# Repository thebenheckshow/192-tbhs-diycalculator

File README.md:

# 192-tbhs-diycalculator
Ben, Felix and Max take us back to 1972 and the invention of the first calculator this week, then decide to hack their own! Watch as they use the Raspberry Pi Compute Module and a Formlabs SLA 3D printer to create their own graphing calculator.

https://www.element14.com/community/docs/DOC-77309/l/episode-192-ben-hecks-diy-calculator-episode

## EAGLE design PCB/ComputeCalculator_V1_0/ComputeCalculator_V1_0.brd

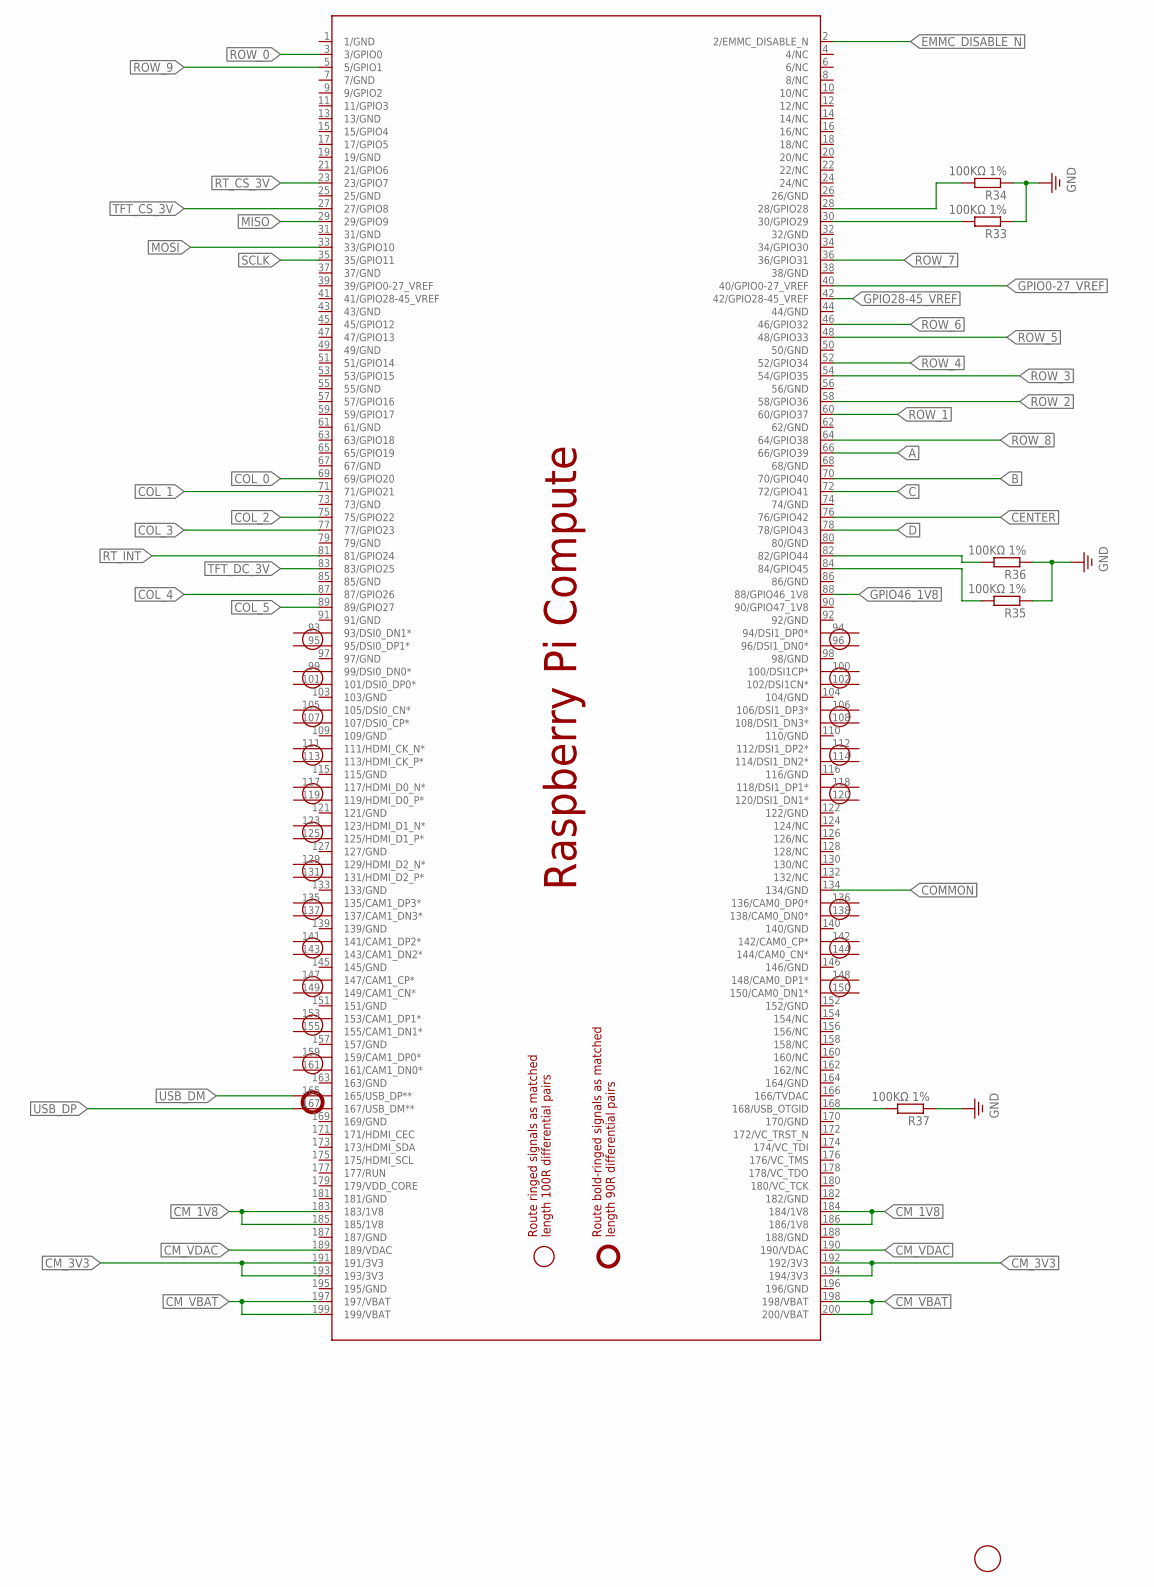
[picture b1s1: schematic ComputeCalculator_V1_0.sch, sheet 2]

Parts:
PCB1: RPI_COMPUTE
R33, R34, R35, R36, R37: 100KΩ 1%; M1206
U$2: FIDUCIAL; FIDUCIAL_1MM

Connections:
A: PCB1.66 (66/GPIO39); also elsewhere on the board
B: PCB1.70 (70/GPIO40); also elsewhere on the board
C: PCB1.72 (72/GPIO41); also elsewhere on the board
CENTER: PCB1.76 (76/GPIO42); also elsewhere on the board
CM_1V8: PCB1.183 (183/1V8), PCB1.184 (184/1V8), PCB1.185 (185/1V8), PCB1.186 (186/1V8); also elsewhere on the board
CM_3V3: PCB1.191 (191/3V3), PCB1.192 (192/3V3), PCB1.193 (193/3V3), PCB1.194 (194/3V3); also elsewhere on the board
CM_VBAT: PCB1.197 (197/VBAT), PCB1.198 (198/VBAT), PCB1.199 (199/VBAT), PCB1.200 (200/VBAT); also elsewhere on the board
CM_VDAC: PCB1.189 (189/VDAC), PCB1.190 (190/VDAC); also elsewhere on the board
COL_0: PCB1.69 (69/GPIO20); also elsewhere on the board
COL_1: PCB1.71 (71/GPIO21); also elsewhere on the board
COL_2: PCB1.75 (75/GPIO22); also elsewhere on the board
COL_3: PCB1.77 (77/GPIO23); also elsewhere on the board
COL_4: PCB1.87 (87/GPIO26); also elsewhere on the board
COL_5: PCB1.89 (89/GPIO27); also elsewhere on the board
COMMON: PCB1.134 (134/GND); also elsewhere on the board
D: PCB1.78 (78/GPIO43); also elsewhere on the board
EMMC_DISABLE_N: PCB1.2 (2/EMMC_DISABLE_N)
GND: R33.1, R34.1, R35.1, R36.1, R37.1; also elsewhere on the board
GPIO0-27_VREF: PCB1.40 (40/GPIO0-27_VREF); also elsewhere on the board
GPIO28-45_VREF: PCB1.42 (42/GPIO28-45_VREF); also elsewhere on the board
GPIO46_1V8: PCB1.88 (88/GPIO46_1V8)
MISO: PCB1.29 (29/GPIO9); also elsewhere on the board
MOSI: PCB1.33 (33/GPIO10); also elsewhere on the board
unnamed: PCB1.28 (28/GPIO28), R34.2
unnamed: PCB1.82 (82/GPIO44), R36.2
unnamed: PCB1.84 (84/GPIO45), R35.2
unnamed: PCB1.168 (168/USB_OTGID), R37.2
unnamed: PCB1.30 (30/GPIO29), R33.2
ROW_0: PCB1.3 (3/GPIO0); also elsewhere on the board
ROW_1: PCB1.60 (60/GPIO37); also elsewhere on the board
ROW_2: PCB1.58 (58/GPIO36); also elsewhere on the board
ROW_3: PCB1.54 (54/GPIO35); also elsewhere on the board
ROW_4: PCB1.52 (52/GPIO34); also elsewhere on the board
ROW_5: PCB1.48 (48/GPIO33); also elsewhere on the board
ROW_6: PCB1.46 (46/GPIO32); also elsewhere on the board
ROW_7: PCB1.36 (36/GPIO31); also elsewhere on the board
ROW_8: PCB1.64 (64/GPIO38); also elsewhere on the board
ROW_9: PCB1.5 (5/GPIO1); also elsewhere on the board
RT_CS_3V: PCB1.23 (23/GPIO7); also elsewhere on the board
RT_INT: PCB1.81 (81/GPIO24); also elsewhere on the board
SCLK: PCB1.35 (35/GPIO11); also elsewhere on the board
TFT_CS_3V: PCB1.27 (27/GPIO8); also elsewhere on the board
TFT_DC_3V: PCB1.83 (83/GPIO25); also elsewhere on the board
USB_DM: PCB1.165 (165/USB_DP**); also elsewhere on the board
USB_DP: PCB1.167 (167/USB_DM**); also elsewhere on the board

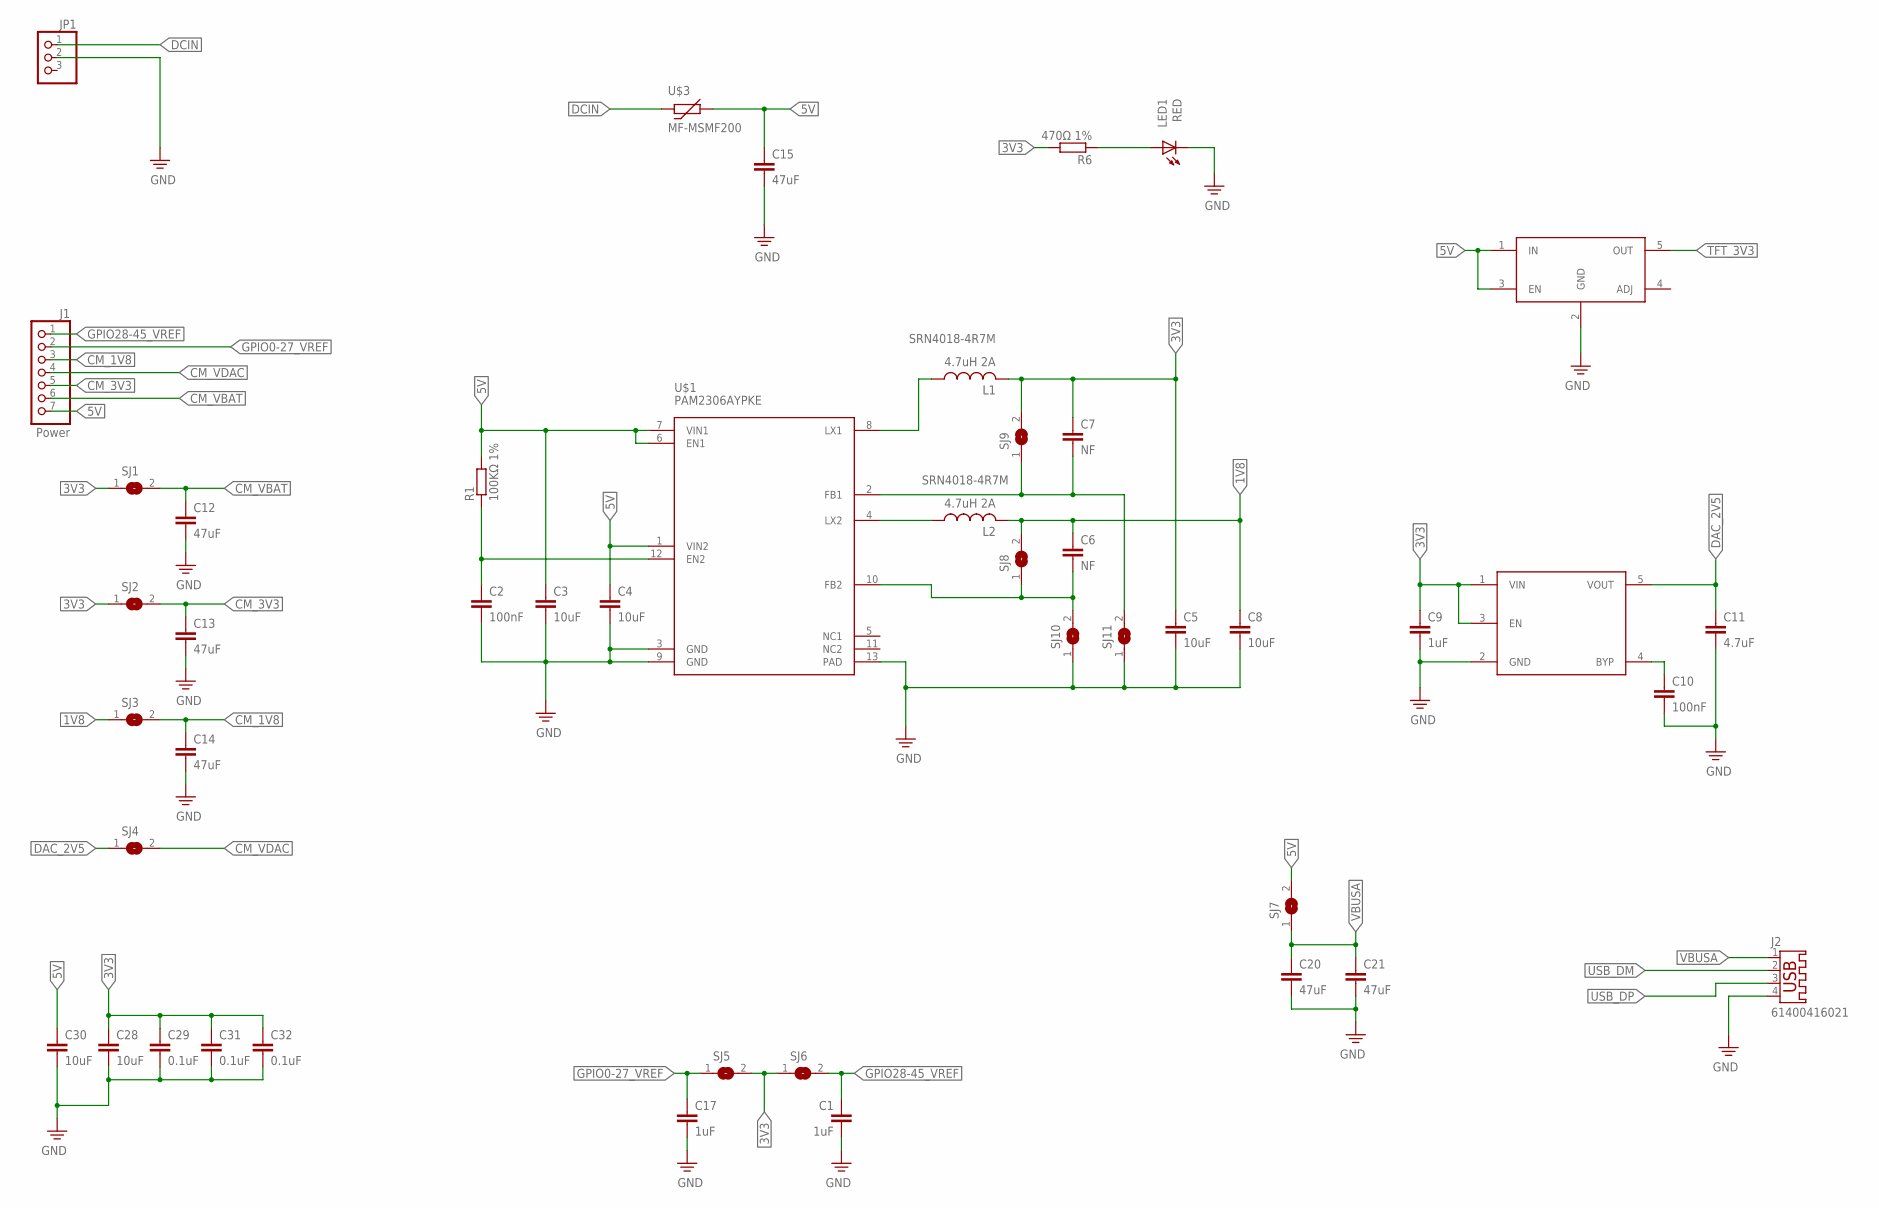
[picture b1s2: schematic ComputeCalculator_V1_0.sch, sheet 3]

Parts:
C1, C9, C17: 1uF; C1206
C2, C10: 100nF; C1206
C3, C4, C5, C8, C28, C30: 10uF; C1206
C6, C7: NF; C1206
C11: 4.7uF; C1206
C12, C13, C14, C20, C21: 47uF; C1206
C15: 47uF; C0603
C29, C31, C32: 0.1uF; C1206
J1: Power; 1X7-BIG
J2: 61400416021; USB-A003
JP1: PINHD-1X3; 1X03
L1, L2: SRN4018-4R7M; POWER-CHOKE_WE-TPC
LED1: RED; CHIP-LED0805
R1: 100KΩ 1%; M1206
R6: 470Ω 1%; M1206
SJ1, SJ2, SJ3, SJ4, SJ5, SJ6, SJ7, SJ8, SJ9, SJ10, SJ11: JUMPER; SJW
U$1: PAM2306AYPKE; WDFN_12L
U$3: MF-MSMF200
U$4: AP7115-25SEG; SOT-25
U$5: MIC5225; SOT-25

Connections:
1V8: C6.1, C8.1, L2.2, SJ3.1, SJ8.2
3V3: C5.1, C7.1, C9.1, C28.1, C29.1, C31.1, C32.1, L1.2, R6.2, SJ1.1, SJ2.1, SJ5.2, SJ6.1, SJ9.2, U$4.1 (VIN), U$4.3 (EN)
5V: C3.1, C4.1, C15.1, C30.1, J1.7, R1.2, SJ7.2, U$1.1 (VIN2), U$1.6 (EN1), U$1.7 (VIN1), U$3.P$2 (2), U$5.1 (IN), U$5.3 (EN)
CM_1V8: C14.1, J1.3, SJ3.2; also elsewhere on the board
CM_3V3: C13.1, J1.5, SJ2.2; also elsewhere on the board
CM_VBAT: C12.1, J1.6, SJ1.2; also elsewhere on the board
CM_VDAC: J1.4, SJ4.2; also elsewhere on the board
DAC_2V5: C11.1, SJ4.1, U$4.5 (VOUT)
DCIN: JP1.1, U$3.P$1 (1)
GND: C1.2, C2.2, C3.2, C4.2, C5.2, C8.2, C9.2, C10.2, C11.2, C12.2, C13.2, C14.2, C15.2, C17.2, C20.2, C21.2, C28.2, C29.2, C30.2, C31.2, C32.2, J2.4, JP1.2, LED1.C, SJ10.1, SJ11.1, U$1.3 (GND), U$1.9 (GND), U$1.13 (PAD), U$4.2 (GND), U$5.2 (GND); also elsewhere on the board
GPIO0-27_VREF: C17.1, J1.2, SJ5.1; also elsewhere on the board
GPIO28-45_VREF: C1.1, J1.1, SJ6.2; also elsewhere on the board
unnamed: C7.2, SJ9.1, SJ11.2, U$1.2 (FB1)
unnamed: LED1.A, R6.1
unnamed: C2.1, R1.1, U$1.12 (EN2)
unnamed: C6.2, SJ8.1, SJ10.2, U$1.10 (FB2)
unnamed: L1.1, U$1.8 (LX1)
unnamed: L2.1, U$1.4 (LX2)
unnamed: C10.1, U$4.4 (BYP)
TFT_3V3: U$5.5 (OUT); also elsewhere on the board
USB_DM: J2.2; also elsewhere on the board
USB_DP: J2.3; also elsewhere on the board
VBUSA: C20.1, C21.1, J2.1, SJ7.1

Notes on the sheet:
4.7uH 2A

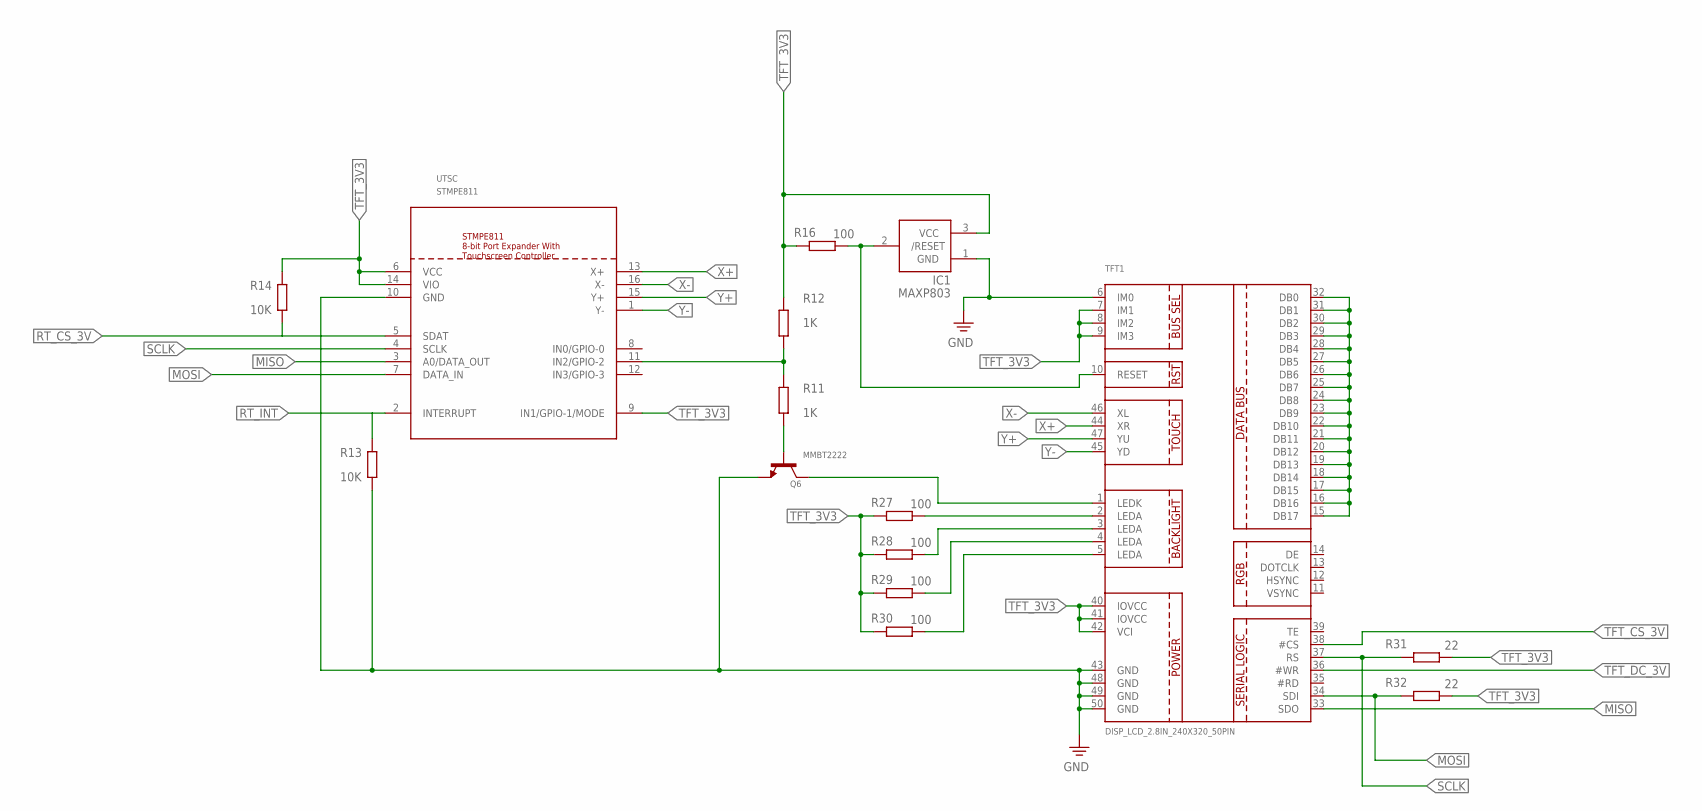
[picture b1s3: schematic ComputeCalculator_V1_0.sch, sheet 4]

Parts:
IC1: MAXP803; SOT23
Q6: MMBT2222; SOT23-WIDE
R11, R12: 1K; M1206
R13, R14: 10K; M1206
R16, R27, R28, R29, R30: 100; M1206
R31, R32: 22; M1206
TFT1: DISP_LCD_2.8IN_240X320_50PIN; TFT_2.83IN_240X320_50PIN
UTSC: STMPE811; QFN16L

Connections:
GND: IC1.1 (GND), Q6.2 (E), R13.2, TFT1.6 (IM0), TFT1.43 (GND), TFT1.48 (GND), TFT1.49 (GND), TFT1.50 (GND), UTSC.10 (GND); also elsewhere on the board
MISO: TFT1.33 (SDO), UTSC.3 (A0/DATA_OUT); also elsewhere on the board
MOSI: R32.2, TFT1.34 (SDI), UTSC.7 (DATA_IN); also elsewhere on the board
unnamed: Q6.3 (C), TFT1.1 (LEDK)
unnamed: R11.1, R12.2, UTSC.11 (IN2/GPIO-2)
unnamed: Q6.1 (B), R11.2
unnamed: R27.1, TFT1.2 (LEDA)
unnamed: R28.1, TFT1.3 (LEDA)
unnamed: R29.1, TFT1.4 (LEDA)
unnamed: R30.1, TFT1.5 (LEDA)
unnamed: TFT1.15 (DB17), TFT1.16 (DB16), TFT1.17 (DB15), TFT1.18 (DB14), TFT1.19 (DB13), TFT1.20 (DB12), TFT1.21 (DB11), TFT1.22 (DB10), TFT1.23 (DB9), TFT1.24 (DB8), TFT1.25 (DB7), TFT1.26 (DB6), TFT1.27 (DB5), TFT1.28 (DB4), TFT1.29 (DB3), TFT1.30 (DB2), TFT1.31 (DB1), TFT1.32 (DB0)
RT_CS_3V: R14.2, UTSC.5 (SDAT); also elsewhere on the board
RT_INT: R13.1, UTSC.2 (INTERRUPT); also elsewhere on the board
SCLK: R31.2, TFT1.37 (RS), UTSC.4 (SCLK); also elsewhere on the board
TFT_3V3: IC1.3 (VCC), R12.1, R14.1, R16.2, R27.2, R28.2, R29.2, R30.2, R31.1, R32.1, TFT1.7 (IM1), TFT1.8 (IM2), TFT1.9 (IM3), TFT1.40 (IOVCC), TFT1.41 (IOVCC), TFT1.42 (VCI), UTSC.6 (VCC), UTSC.9 (IN1/GPIO-1/MODE), UTSC.14 (VIO); also elsewhere on the board
TFT_CS_3V: TFT1.38 (#CS); also elsewhere on the board
TFT_DC_3V: TFT1.36 (#WR); also elsewhere on the board
TFT_RESET: IC1.2 (/RESET), R16.1, TFT1.10 (RESET)
X+: TFT1.44 (XR), UTSC.13 (X+)
X-: TFT1.46 (XL), UTSC.16 (X-)
Y+: TFT1.47 (YU), UTSC.15 (Y+)
Y-: TFT1.45 (YD), UTSC.1 (Y-)

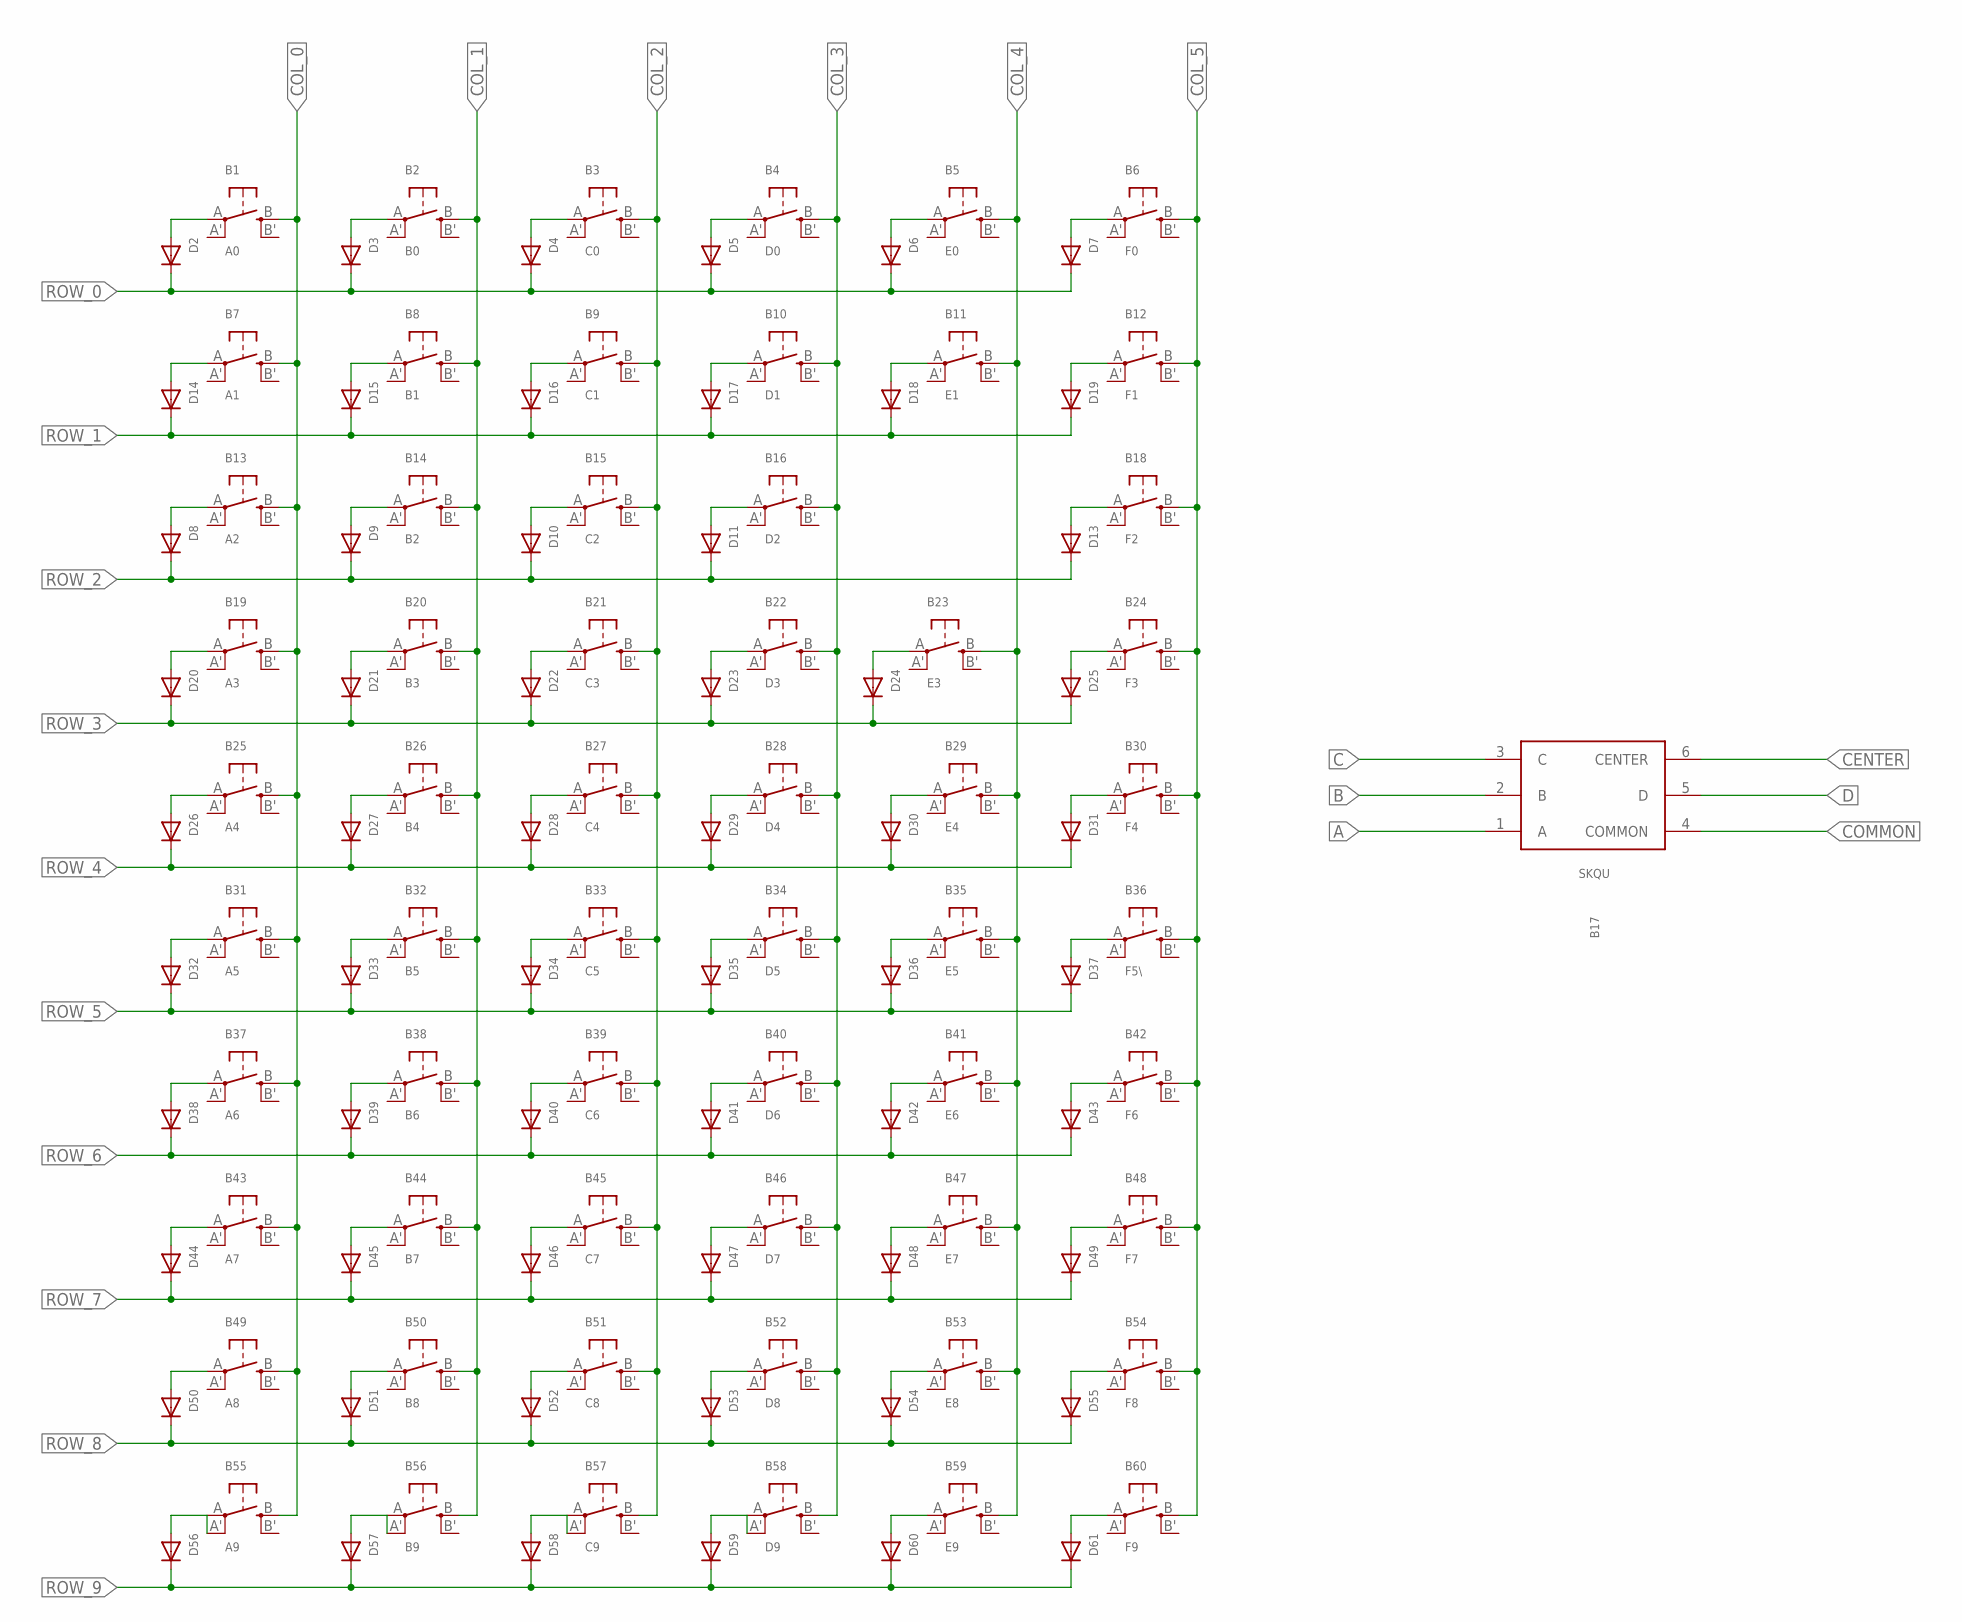
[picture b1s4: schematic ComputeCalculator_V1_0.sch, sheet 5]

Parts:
B1: A0; EVQ-Q2
B2: B0; EVQ-Q2
B3: C0; EVQ-Q2
B4: D0; EVQ-Q2
B5: E0; EVQ-Q2
B6: F0; EVQ-Q2
B7: A1; EVQ-Q2
B8: B1; EVQ-Q2
B9: C1; EVQ-Q2
B10: D1; EVQ-Q2
B11: E1; EVQ-Q2
B12: F1; EVQ-Q2
B13: A2; EVQ-Q2
B14: B2; EVQ-Q2
B15: C2; EVQ-Q2
B16: D2; EVQ-Q2
B17: SKQU
B18: F2; EVQ-Q2
B19: A3; EVQ-Q2
B20: B3; EVQ-Q2
B21: C3; EVQ-Q2
B22: D3; EVQ-Q2
B23: E3; EVQ-Q2
B24: F3; EVQ-Q2
B25: A4; EVQ-Q2
B26: B4; EVQ-Q2
B27: C4; EVQ-Q2
B28: D4; EVQ-Q2
B29: E4; EVQ-Q2
B30: F4; EVQ-Q2
B31: A5; EVQ-Q2
B32: B5; EVQ-Q2
B33: C5; EVQ-Q2
B34: D5; EVQ-Q2
B35: E5; EVQ-Q2
B36: F5\; EVQ-Q2
B37: A6; EVQ-Q2
B38: B6; EVQ-Q2
B39: C6; EVQ-Q2
B40: D6; EVQ-Q2
B41: E6; EVQ-Q2
B42: F6; EVQ-Q2
B43: A7; EVQ-Q2
B44: B7; EVQ-Q2
B45: C7; EVQ-Q2
B46: D7; EVQ-Q2
B47: E7; EVQ-Q2
B48: F7; EVQ-Q2
B49: A8; EVQ-Q2
B50: B8; EVQ-Q2
B51: C8; EVQ-Q2
B52: D8; EVQ-Q2
B53: E8; EVQ-Q2
B54: F8; EVQ-Q2
B55: A9; EVQ-Q2
B56: B9; EVQ-Q2
B57: C9; EVQ-Q2
B58: D9; EVQ-Q2
B59: E9; EVQ-Q2
B60: F9; EVQ-Q2
D2, D3, D4, D5, D6, D7, D8, D9, D10, D11, D13, D14, D15, D16, D17, D18, D19, D20, D21, D22, D23, D24, D25, D26, D27, D28, D29, D30, D31, D32, D33, D34, D35, D36, D37, D38, D39, D40, D41, D42, D43, D44, D45, D46, D47, D48, D49, D50, D51, D52, D53, D54, D55, D56, D57, D58, D59, D60, D61: DIODESMA; SMADIODE

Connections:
A: B17.1 (A); also elsewhere on the board
B: B17.2 (B); also elsewhere on the board
C: B17.3 (C); also elsewhere on the board
CENTER: B17.6 (CENTER); also elsewhere on the board
COL_0: B1.B (S), B7.B (S), B13.B (S), B19.B (S), B25.B (S), B31.B (S), B37.B (S), B43.B (S), B49.B (S), B55.B (S); also elsewhere on the board
COL_1: B2.B (S), B8.B (S), B14.B (S), B20.B (S), B26.B (S), B32.B (S), B38.B (S), B44.B (S), B50.B (S), B56.B (S); also elsewhere on the board
COL_2: B3.B (S), B9.B (S), B15.B (S), B21.B (S), B27.B (S), B33.B (S), B39.B (S), B45.B (S), B51.B (S), B57.B (S); also elsewhere on the board
COL_3: B4.B (S), B10.B (S), B16.B (S), B22.B (S), B28.B (S), B34.B (S), B40.B (S), B46.B (S), B52.B (S), B58.B (S); also elsewhere on the board
COL_4: B5.B (S), B11.B (S), B23.B (S), B29.B (S), B35.B (S), B41.B (S), B47.B (S), B53.B (S), B59.B (S); also elsewhere on the board
COL_5: B6.B (S), B12.B (S), B18.B (S), B24.B (S), B30.B (S), B36.B (S), B42.B (S), B48.B (S), B54.B (S), B60.B (S); also elsewhere on the board
COMMON: B17.4 (COMMON); also elsewhere on the board
D: B17.5 (D); also elsewhere on the board
unnamed: B6.A, D7.A
unnamed: B2.A, D3.A
unnamed: B3.A, D4.A
unnamed: B1.A, D2.A
unnamed: B4.A, D5.A
unnamed: B5.A, D6.A
unnamed: B13.A, D8.A
unnamed: B18.A, D13.A
unnamed: B14.A, D9.A
unnamed: B15.A, D10.A
unnamed: B16.A, D11.A
unnamed: B23.A, D24.A
unnamed: B7.A, D14.A
unnamed: B12.A, D19.A
unnamed: B8.A, D15.A
unnamed: B9.A, D16.A
unnamed: B10.A, D17.A
unnamed: B11.A, D18.A
unnamed: B19.A, D20.A
unnamed: B24.A, D25.A
unnamed: B20.A, D21.A
unnamed: B21.A, D22.A
unnamed: B22.A, D23.A
unnamed: B25.A, D26.A
unnamed: B30.A, D31.A
unnamed: B26.A, D27.A
unnamed: B27.A, D28.A
unnamed: B28.A, D29.A
unnamed: B29.A, D30.A
unnamed: B31.A, D32.A
unnamed: B36.A, D37.A
unnamed: B32.A, D33.A
unnamed: B33.A, D34.A
unnamed: B34.A, D35.A
unnamed: B35.A, D36.A
unnamed: B37.A, D38.A
unnamed: B42.A, D43.A
unnamed: B38.A, D39.A
unnamed: B39.A, D40.A
unnamed: B40.A, D41.A
unnamed: B41.A, D42.A
unnamed: B43.A, D44.A
unnamed: B48.A, D49.A
unnamed: B44.A, D45.A
unnamed: B45.A, D46.A
unnamed: B46.A, D47.A
unnamed: B47.A, D48.A
unnamed: B49.A, D50.A
unnamed: B54.A, D55.A
unnamed: B50.A, D51.A
unnamed: B51.A, D52.A
unnamed: B52.A, D53.A
unnamed: B53.A, D54.A
unnamed: B55.A, B55.A' (P1), D56.A
unnamed: B60.A, D61.A
unnamed: B56.A, B56.A' (P1), D57.A
unnamed: B57.A, B57.A' (P1), D58.A
unnamed: B58.A, B58.A' (P1), D59.A
unnamed: B59.A, D60.A
ROW_0: D2.C, D3.C, D4.C, D5.C, D6.C, D7.C; also elsewhere on the board
ROW_1: D14.C, D15.C, D16.C, D17.C, D18.C, D19.C; also elsewhere on the board
ROW_2: D8.C, D9.C, D10.C, D11.C, D13.C; also elsewhere on the board
ROW_3: D20.C, D21.C, D22.C, D23.C, D24.C, D25.C; also elsewhere on the board
ROW_4: D26.C, D27.C, D28.C, D29.C, D30.C, D31.C; also elsewhere on the board
ROW_5: D32.C, D33.C, D34.C, D35.C, D36.C, D37.C; also elsewhere on the board
ROW_6: D38.C, D39.C, D40.C, D41.C, D42.C, D43.C; also elsewhere on the board
ROW_7: D44.C, D45.C, D46.C, D47.C, D48.C, D49.C; also elsewhere on the board
ROW_8: D50.C, D51.C, D52.C, D53.C, D54.C, D55.C; also elsewhere on the board
ROW_9: D56.C, D57.C, D58.C, D59.C, D60.C, D61.C; also elsewhere on the board

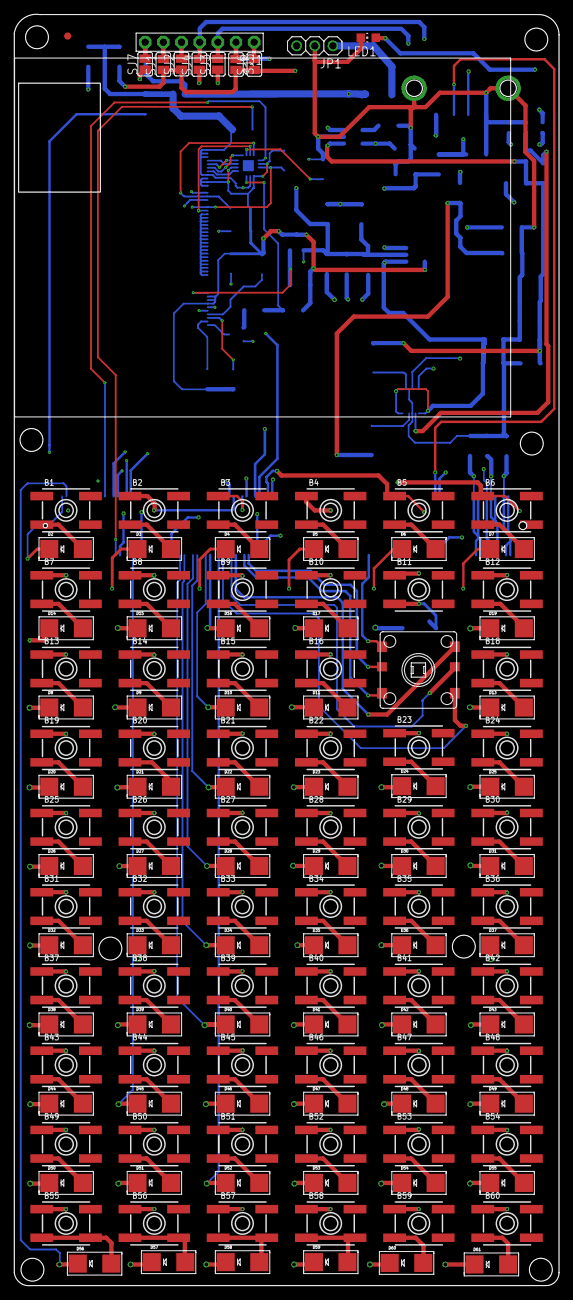
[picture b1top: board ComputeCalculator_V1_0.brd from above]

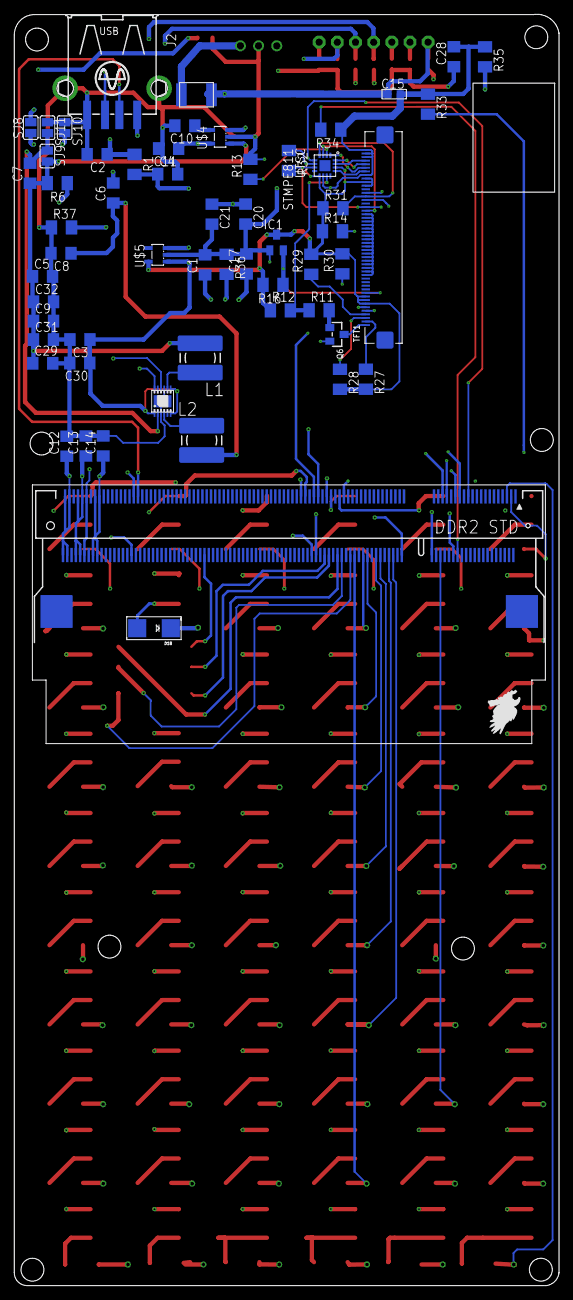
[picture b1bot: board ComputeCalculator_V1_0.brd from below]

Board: 4 copper layers, 76.2 x 177.9 mm, 187 parts (57 on the bottom side), 129 nets.

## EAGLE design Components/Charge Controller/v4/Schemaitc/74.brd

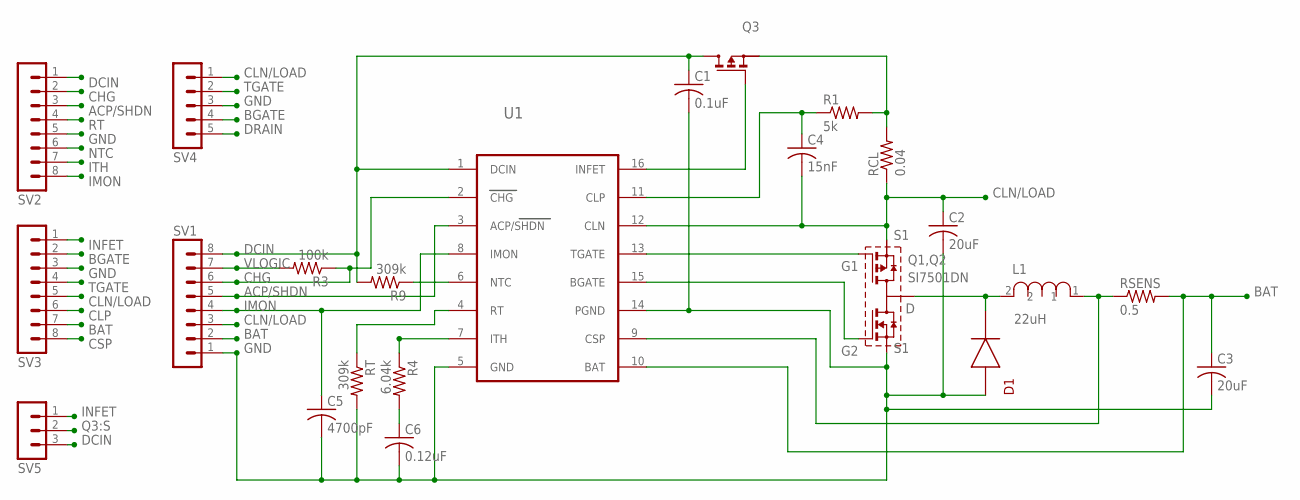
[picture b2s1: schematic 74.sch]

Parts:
C1: 0.1uF; C1210
C2, C3: 20uF; C1210
C4: 15nF; C1210
C5: 4700pF; C1210
C6: 0.12uF; C1210
D1: DIODE
L1: 22uH; POWERINDUCTOR
Q1,Q2: SI7501DN; POWERPAK
Q3: MOSFET; SOT-23
R1: 5k; R1206
R3: 100k; R1206
R4: 6.04k; R1206
R9: 309k; R1206
RCL: 0.04; R1206
RSENS: 0.5; 0612/1632
RT: 309k; R1206
SV1, SV2, SV3: MA08-1
SV4: MA05-1
SV5: MA03-1
U1: LTC6004; SSOP-16

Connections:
ACP/SHDN: SV1.5, SV2.3, U1.3 (ACP/SHDN)
BAT: C3.1, RSENS.2, SV1.2, SV3.7, U1.10 (BAT)
BGATE: Q1,Q2.G2, SV3.2, SV4.4, U1.15 (BGATE)
CHG: R3.1, SV1.6, SV2.2, U1.2 (CHG)
CLN/LOAD: C2.1, C4.2, Q1,Q2.S1, RCL.1, SV1.3, SV3.5, SV4.1, U1.12 (CLN)
CLP: C4.1, R1.1, SV3.6, U1.11 (CLP)
CSP: L1.1, RSENS.1, SV3.8, U1.9 (CSP)
DCIN: C1.1, Q3.DRAIN (D), R9.2, SV1.8, SV2.1, SV5.3, U1.1 (DCIN)
DRAIN: D1.P$2 (2), L1.2, Q1,Q2.D, SV4.5
GND: C1.2, C2.2, C3.2, C5.2, C6.2, D1.P$1 (1), Q1,Q2.S2, RT.2, SV1.1, SV2.5, SV3.3, SV4.3, U1.5 (GND), U1.14 (PGND)
IMON: C5.1, SV1.4, SV2.8, U1.8 (IMON)
INFET: Q3.GATE (G), SV3.1, SV5.1, U1.16 (INFET)
ITH: R4.1, SV2.7, U1.7 (ITH)
unnamed: C6.1, R4.2
NTC: R9.1, SV2.6, U1.6 (NTC)
Q3:S: Q3.SOURCE (S), R1.2, RCL.2, SV5.2
RT: RT.1, SV2.4, U1.4 (RT)
TGATE: Q1,Q2.G1, SV3.4, SV4.2, U1.13 (TGATE)
VLOGIC: R3.2, SV1.7

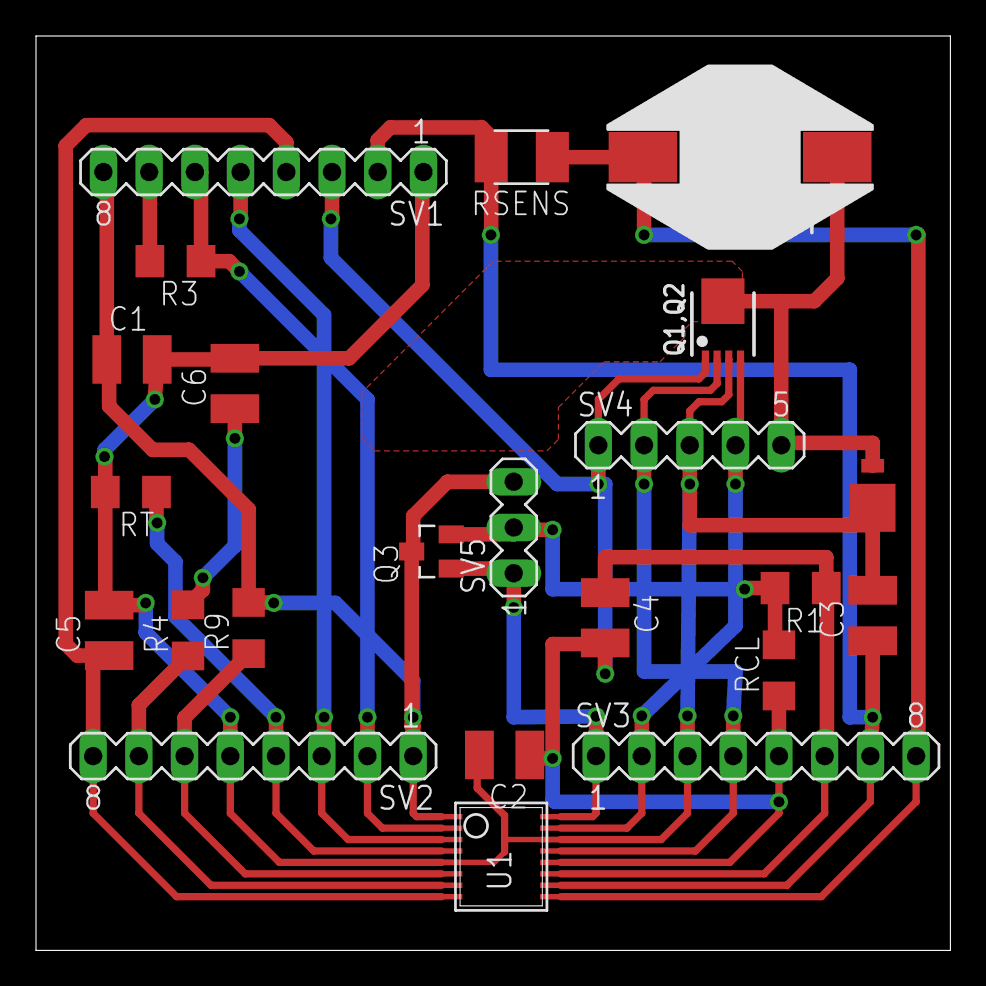
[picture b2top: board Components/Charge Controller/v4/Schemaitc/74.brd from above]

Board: 2 copper layers, 50.8 x 50.8 mm, 23 parts (0 on the bottom side), 19 nets.

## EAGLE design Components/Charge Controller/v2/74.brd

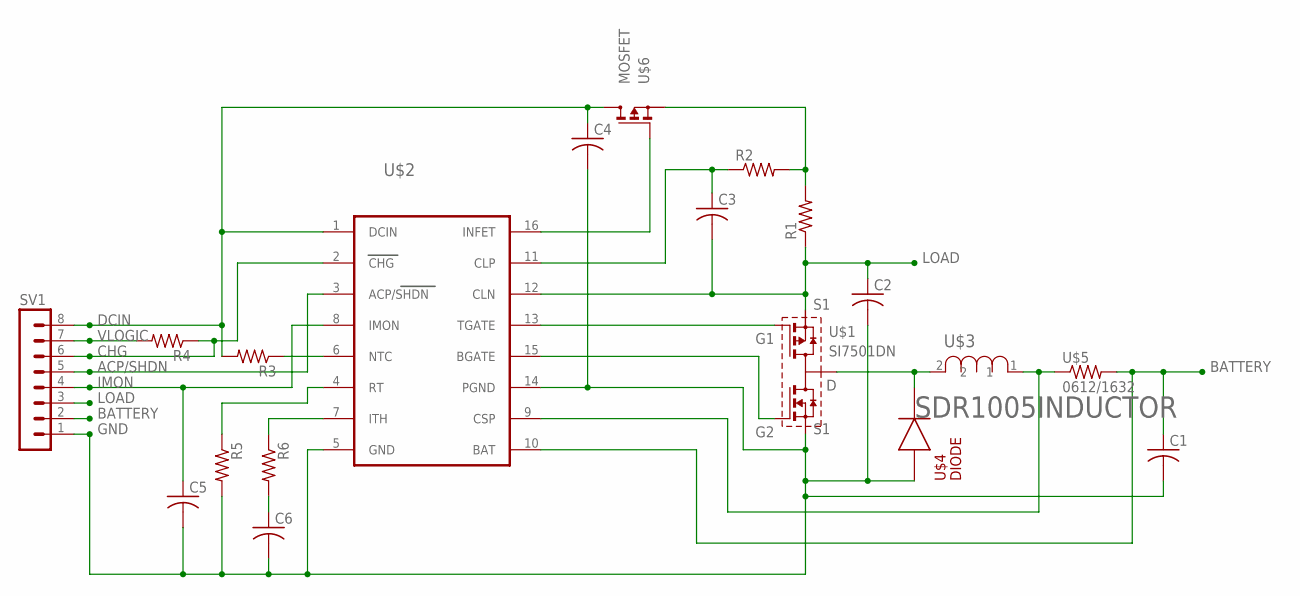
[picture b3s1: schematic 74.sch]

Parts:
C1, C2, C3, C4, C5, C6: C-USC1210; C1210
R1, R2, R3, R4, R5, R6: R-US_R1206; R1206
SV1: MA08-1
U$1: SI7501DN; POWERPAK
U$2: LTC6004; SSOP-16
U$3: SDR1005INDUCTOR; POWERINDUCTOR
U$4: DIODE
U$5: 0612/1632
U$6: MOSFET; SOT-23

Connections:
ACP/SHDN: SV1.5, U$2.3 (ACP/SHDN)
BATTERY: C1.1, SV1.2, U$2.10 (BAT), U$5.2
CHG: R4.1, SV1.6, U$2.2 (CHG)
DCIN: C4.1, R3.2, SV1.8, U$2.1 (DCIN), U$6.DRAIN (D)
GND: C1.2, C2.2, C4.2, C5.2, C6.2, R5.2, SV1.1, U$1.S2, U$2.5 (GND), U$2.14 (PGND), U$4.P$1 (1)
IMON: C5.1, SV1.4, U$2.8 (IMON)
LOAD: C2.1, C3.2, R1.1, SV1.3, U$1.S1, U$2.12 (CLN)
unnamed: U$1.G1, U$2.13 (TGATE)
unnamed: U$1.G2, U$2.15 (BGATE)
unnamed: U$1.D, U$3.2, U$4.P$2 (2)
unnamed: U$2.9 (CSP), U$3.1, U$5.1
unnamed: C3.1, R2.1, U$2.11 (CLP)
unnamed: R1.2, R2.2, U$6.SOURCE (S)
unnamed: U$2.16 (INFET), U$6.GATE (G)
unnamed: R6.1, U$2.7 (ITH)
unnamed: R3.1, U$2.6 (NTC)
unnamed: C6.1, R6.2
unnamed: R5.1, U$2.4 (RT)
VLOGIC: R4.2, SV1.7

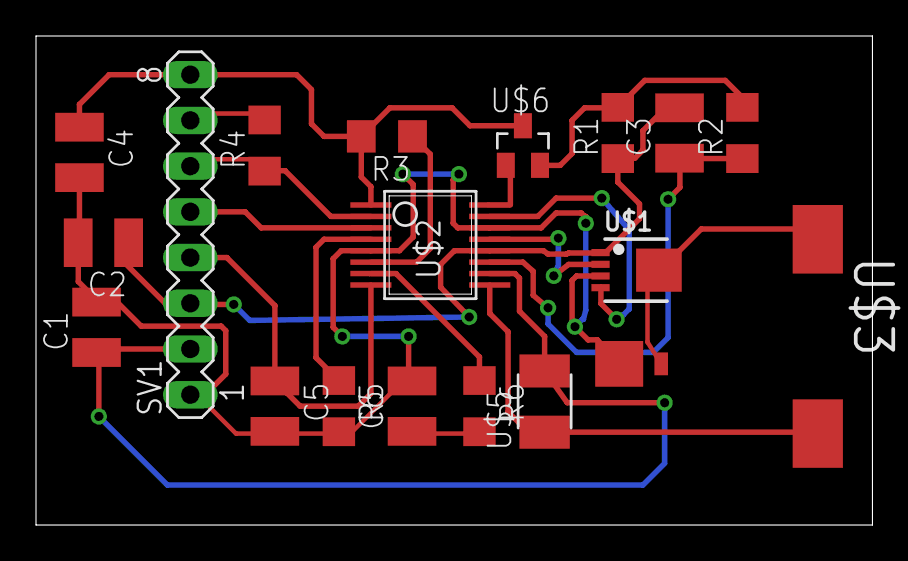
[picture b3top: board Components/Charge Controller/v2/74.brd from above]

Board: 2 copper layers, 46.5 x 27.2 mm, 19 parts (0 on the bottom side), 19 nets.

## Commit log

2020-04-15 Initial

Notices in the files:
parts and their libraries:
microbuilder: This work is placed in the public domain, and may be freely used for commercial and non-commercial work with the following conditions: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
